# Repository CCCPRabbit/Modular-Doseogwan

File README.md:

# Modular Doseogwan

## Introduction

This project includes KiCad symbols, schematics, and program libraries.

## Contents

- KiCad Symbols
- Schematics
- Program Libraries

## License

This project is licensed under **CC-BY-NC-SA 4.0**.

- **BY** (Attribution): You must give appropriate credit to the original author.
- **NC** (NonCommercial): You may not use the material for commercial purposes.
- **SA** (ShareAlike): If you remix, transform, or build upon the material, you must distribute your contributions under the same license.

For more details, see the [Creative Commons license page](https://creativecommons.org/licenses/by-nc-sa/4.0/).

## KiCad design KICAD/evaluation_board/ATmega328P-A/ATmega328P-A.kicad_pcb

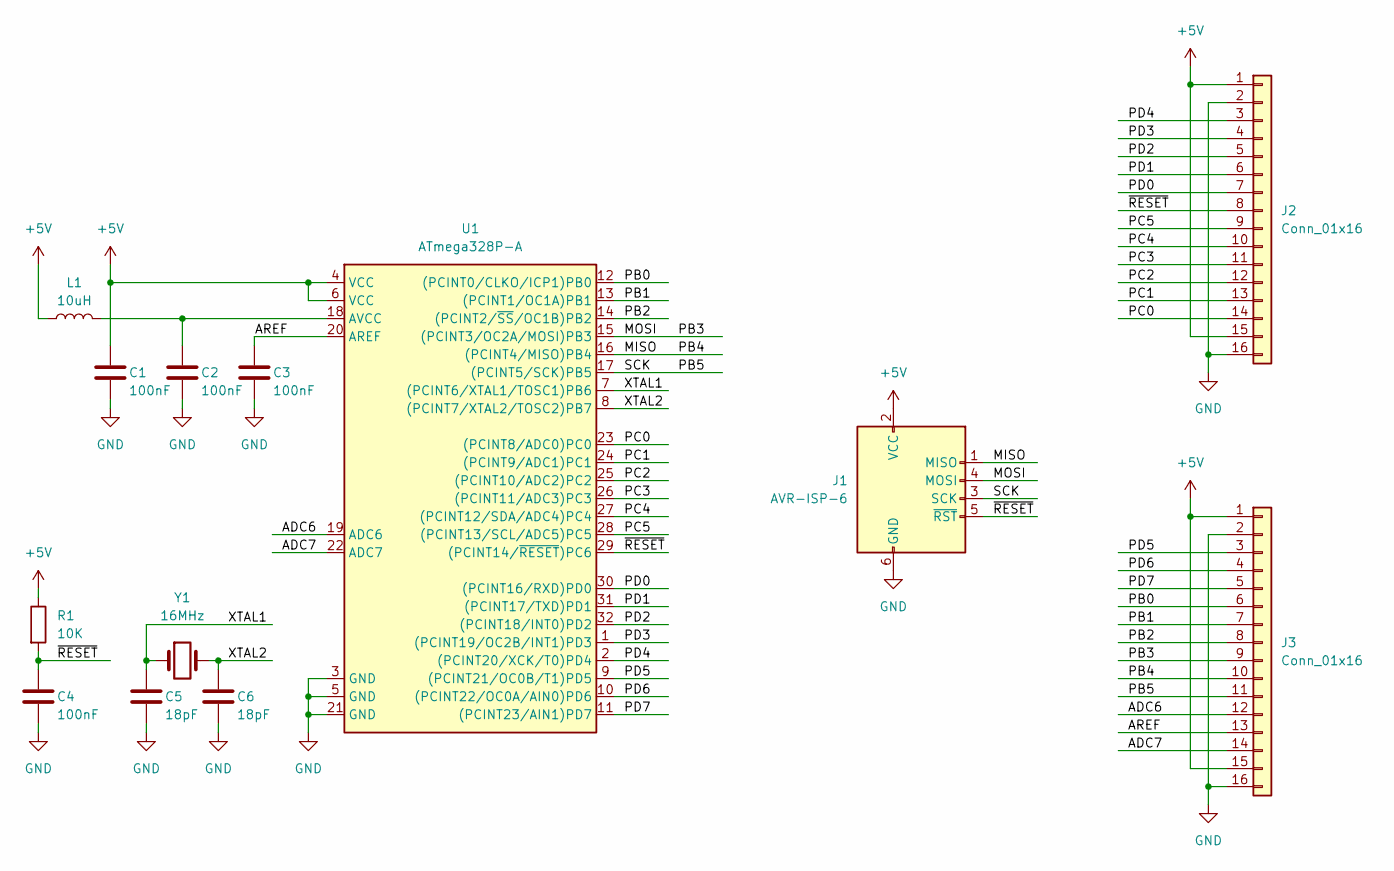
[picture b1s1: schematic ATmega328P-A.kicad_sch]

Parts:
C1, C2, C3, C4: 100nF; C_0603_1608Metric
C5, C6: 18pF; C_0603_1608Metric
J1: AVR-ISP-6; IDC-Header_2x03_P2.54mm_Vertical
J2, J3: Conn_01x16; PinHeader_1x16_P2.54mm_Vertical
L1: 10uH; L_0603_1608Metric
R1: 10K; R_0603_1608Metric
U1: ATmega328P-A; TQFP-32_7x7mm_P0.8mm
Y1: 16MHz; Crystal_SMD_HC49-SD

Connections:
+5V: C1.1, J1.2 (VCC), J2.1, J2.15, J3.1, J3.15, L1.1, R1.1, U1.4 (VCC), U1.6 (VCC)
/ADC6: J3.12, U1.19 (ADC6)
/ADC7: J3.14, U1.22 (ADC7)
/AREF: C3.1, J3.13, U1.20 (AREF)
/MISO: J1.1 (MISO), J3.10, U1.16 ((PCINT4/MISO)PB4)
/MOSI: J1.4 (MOSI), J3.9, U1.15 ((PCINT3/OC2A/MOSI)PB3)
/PB0: J3.6, U1.12 ((PCINT0/CLKO/ICP1)PB0)
/PB1: J3.7, U1.13 ((PCINT1/OC1A)PB1)
/PB2: J3.8, U1.14 ((PCINT2/~SS/OC1B)PB2)
/PB5: J1.3 (SCK), J3.11, U1.17 ((PCINT5/SCK)PB5)
/PC0: J2.14, U1.23 ((PCINT8/ADC0)PC0)
/PC1: J2.13, U1.24 ((PCINT9/ADC1)PC1)
/PC2: J2.12, U1.25 ((PCINT10/ADC2)PC2)
/PC3: J2.11, U1.26 ((PCINT11/ADC3)PC3)
/PC4: J2.10, U1.27 ((PCINT12/SDA/ADC4)PC4)
/PC5: J2.9, U1.28 ((PCINT13/SCL/ADC5)PC5)
/PD0: J2.7, U1.30 ((PCINT16/RXD)PD0)
/PD1: J2.6, U1.31 ((PCINT17/TXD)PD1)
/PD2: J2.5, U1.32 ((PCINT18/INT0)PD2)
/PD3: J2.4, U1.1 ((PCINT19/OC2B/INT1)PD3)
/PD4: J2.3, U1.2 ((PCINT20/XCK/T0)PD4)
/PD5: J3.3, U1.9 ((PCINT21/OC0B/T1)PD5)
/PD6: J3.4, U1.10 ((PCINT22/OC0A/AIN0)PD6)
/PD7: J3.5, U1.11 ((PCINT23/AIN1)PD7)
/XTAL1: C5.1, U1.7 ((PCINT6/XTAL1/TOSC1)PB6), Y1.1
/XTAL2: C6.1, U1.8 ((PCINT7/XTAL2/TOSC2)PB7), Y1.2
/~RESET: C4.1, J1.5 (~RST), J2.8, R1.2, U1.29 ((PCINT14/~RESET)PC6)
GND: C1.2, C2.2, C3.2, C4.2, C5.2, C6.2, J1.6 (GND), J2.2, J2.16, J3.2, J3.16, U1.3 (GND), U1.5 (GND), U1.21 (GND)
unnamed: C2.1, L1.2, U1.18 (AVCC)

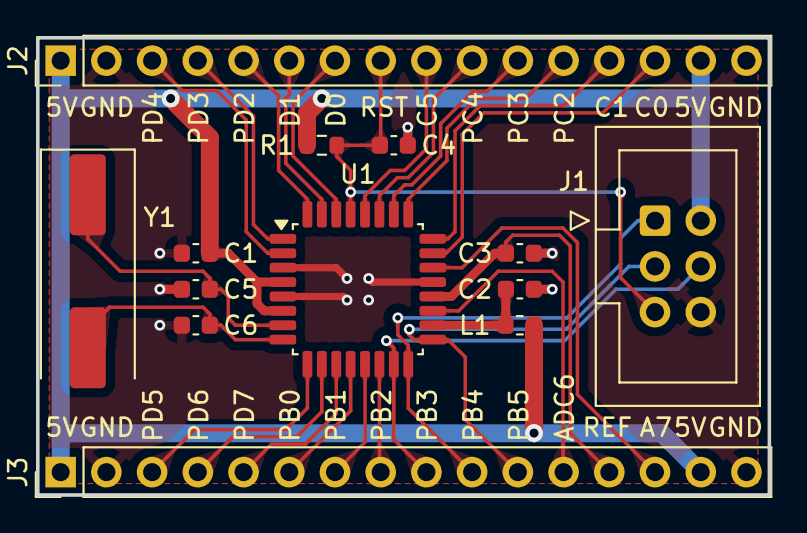
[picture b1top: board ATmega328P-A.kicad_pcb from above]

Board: 2 copper layers, 40.6 x 25.4 mm, 13 parts (0 on the bottom side), 29 nets.

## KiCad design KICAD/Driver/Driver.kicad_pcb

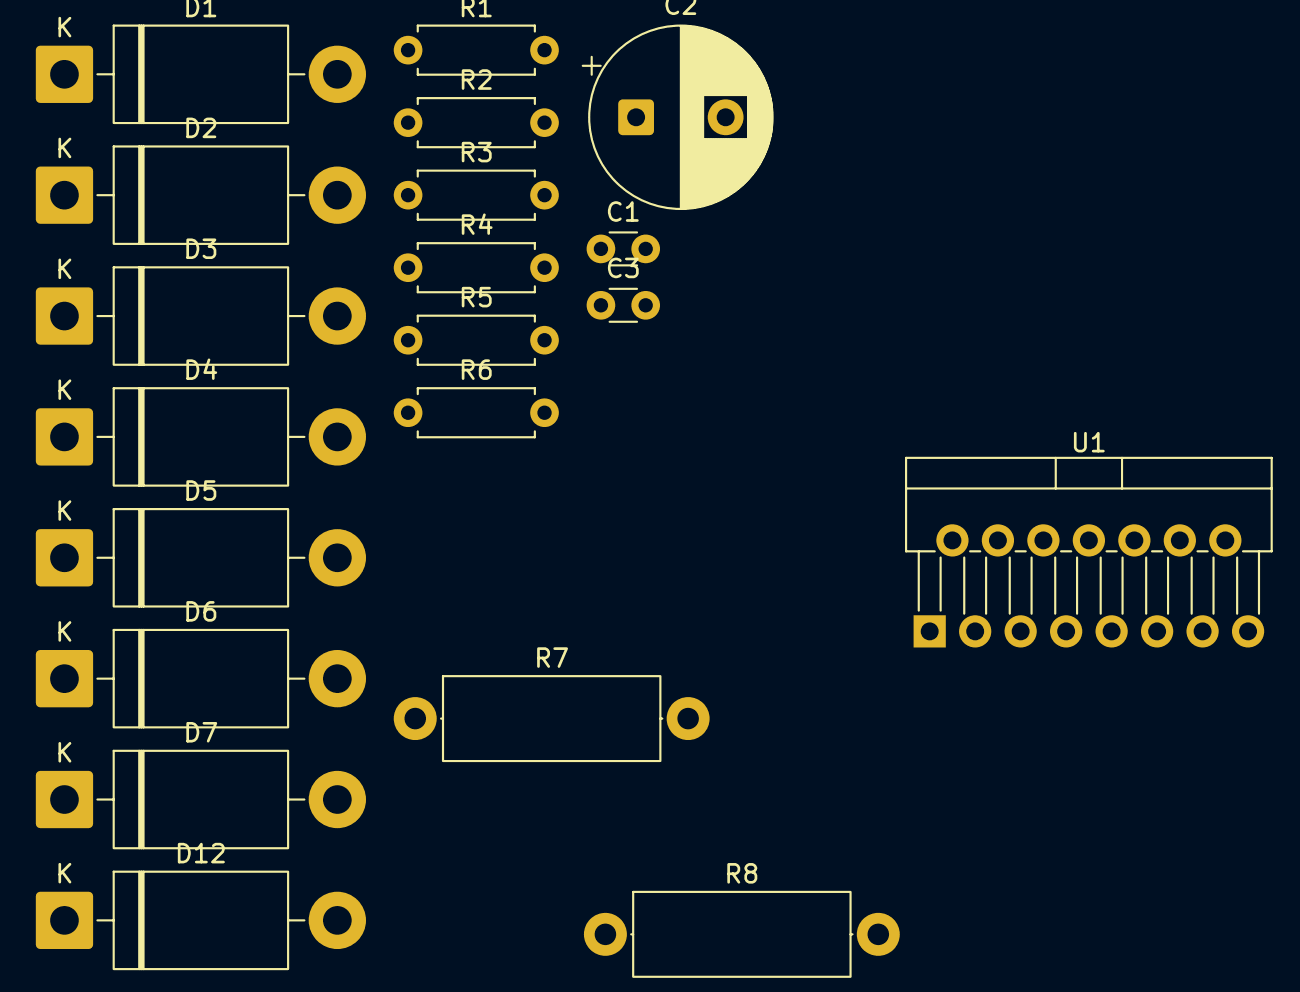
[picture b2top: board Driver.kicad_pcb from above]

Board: 2 copper layers, 20 parts (0 on the bottom side), 15 nets, no tracks yet.

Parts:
C1, C3: 100nF; C_Disc_D3.0mm_W1.6mm_P2.50mm
C2: 470uF/50V; CP_Radial_D10.0mm_P5.00mm
D1, D2, D3, D4, D5, D6, D7, D12: 1N5822; D_DO-201AD_P15.24mm_Horizontal
R1, R2, R3, R4, R5, R6: 100; R_Axial_DIN0207_L6.3mm_D2.5mm_P7.62mm_Horizontal
R7, R8: 0.25/1W; R_Axial_DIN0414_L11.9mm_D4.5mm_P15.24mm_Horizontal
U1: L298N; TO-220-15_P2.54x5.08mm_StaggerOdd_Lead4.58mm_Vertical

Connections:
+5V: C1.1, U1.9 (Vss)
+36V: C2.1, C3.1, D1.1 (K), D2.1 (K), D3.1 (K), D12.1 (K), U1.4 (Vs)
/L298/OUT1: D4.1 (K), D12.2 (A), U1.2 (OUT1)
/L298/OUT2: D1.2 (A), D5.1 (K), U1.3 (OUT2)
/L298/OUT3: D2.2 (A), D6.1 (K), U1.13 (OUT3)
/L298/OUT4: D3.2 (A), D7.1 (K), U1.14 (OUT4)
/L298/SENSE_A: R8.1, U1.1 (SENSE_A)
/L298/SENSE_B: R7.1, U1.15 (SENSE_B)
GND: C1.2, C2.2, C3.2, D4.2 (A), D5.2 (A), D6.2 (A), D7.2 (A), R7.2, R8.2, U1.8 (GND)
unnamed: R3.2, U1.6 (EnA)
unnamed: R6.2, U1.11 (EnB)
unnamed: R1.2, U1.5 (IN1)
unnamed: R2.2, U1.7 (IN2)
unnamed: R4.2, U1.10 (IN3)
unnamed: R5.2, U1.12 (IN4)

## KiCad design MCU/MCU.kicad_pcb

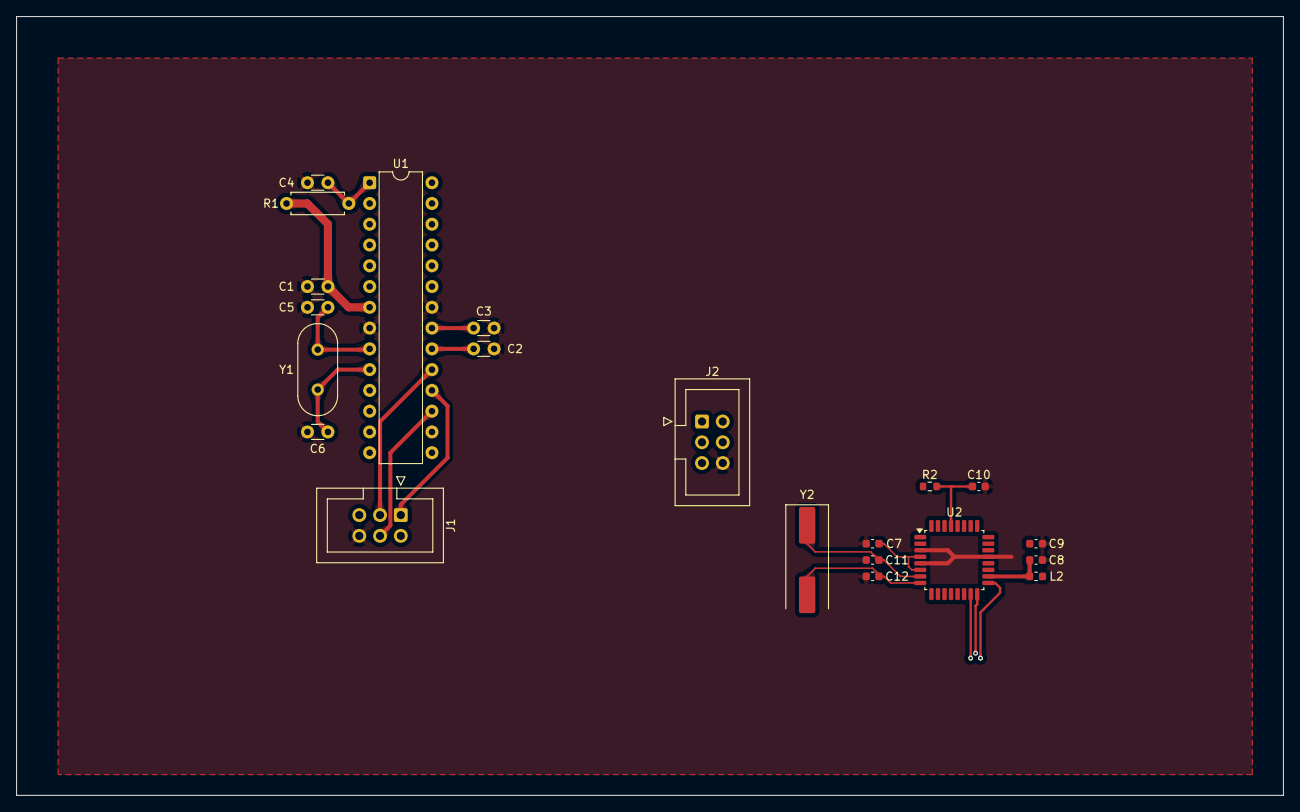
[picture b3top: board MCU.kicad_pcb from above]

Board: 2 copper layers, 154.9 x 95.2 mm, 21 parts (0 on the bottom side), 18 nets.

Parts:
C1, C2, C3, C4: 100nF; C_Disc_D3.0mm_W1.6mm_P2.50mm
C5, C6: 18pF; C_Disc_D3.0mm_W1.6mm_P2.50mm
C7, C8, C9, C10: 100nF; C_0603_1608Metric
C11, C12: 18pF; C_0603_1608Metric
J1, J2: AVR-ISP-6; IDC-Header_2x03_P2.54mm_Vertical
L2: 10uH; L_0603_1608Metric
R1: 10K; R_Axial_DIN0207_L6.3mm_D2.5mm_P7.62mm_Horizontal
R2: 10K; R_0603_1608Metric
U1: ATmega328P-P; DIP-28_W7.62mm
U2: ATmega328P-A; TQFP-32_7x7mm_P0.8mm
Y1: 16MHz/HC49-4H; Crystal_HC49-4H_Vertical
Y2: 16MHz/HC49-SD; Crystal_SMD_HC49-SD

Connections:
+5V: C1.1, C7.1, J1.2 (VCC), J2.2 (VCC), L2.1, R1.1, R2.1, U1.7 (VCC), U2.4 (VCC), U2.6 (VCC)
/ATmega328P-A/MISO: J2.1 (MISO), U2.16 ((PCINT4/MISO)PB4)
/ATmega328P-A/MOSI: J2.4 (MOSI), U2.15 ((PCINT3/OC2A/MOSI)PB3)
/ATmega328P-A/SCK: J2.3 (SCK), U2.17 ((PCINT5/SCK)PB5)
/ATmega328P-A/XTAL1: C11.1, U2.7 ((PCINT6/XTAL1/TOSC1)PB6), Y2.1
/ATmega328P-A/XTAL2: C12.1, U2.8 ((PCINT7/XTAL2/TOSC2)PB7), Y2.2
/ATmega328P-A/~RESET: C10.1, J2.5 (~RST), R2.2, U2.29 ((PCINT14/~RESET)PC6)
/ATmega328P-P/MISO: J1.1 (MISO), U1.18 ((PCINT4/MISO)PB4)
/ATmega328P-P/MOSI: J1.4 (MOSI), U1.17 ((PCINT3/OC2A/MOSI)PB3)
/ATmega328P-P/SCK: J1.3 (SCK), U1.19 ((PCINT5/SCK)PB5)
/ATmega328P-P/XTAL1: C5.1, U1.9 ((PCINT6/XTAL1/TOSC1)PB6), Y1.1
/ATmega328P-P/XTAL2: C6.1, U1.10 ((PCINT7/XTAL2/TOSC2)PB7), Y1.2
/ATmega328P-P/~RESET: C4.1, J1.5 (~RST), R1.2, U1.1 ((PCINT14/~RESET)PC6)
GND: C1.2, C2.2, C3.2, C4.2, C5.2, C6.2, C7.2, C8.2, C9.2, C10.2, C11.2, C12.2, J1.6 (GND), J2.6 (GND), U1.8 (GND), U1.22 (GND), U2.3 (GND), U2.5 (GND), U2.21 (GND)
unnamed: C3.1, U1.21 (AREF)
unnamed: C2.1, U1.20 (AVCC)
unnamed: C9.1, U2.20 (AREF)
unnamed: C8.1, L2.2, U2.18 (AVCC)

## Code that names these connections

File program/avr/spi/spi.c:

#include <avr/io.h>

#define SCK_DDR     DDRB
#define SCK_PIN     PB5
#define MOSI_DDR    DDRB
#define MOSI_PIN    PB3
#define MISO_DDR    DDRB
#define MISO_PIN    PB4
#define CS_DDR      DDRB
#define CS_PORT     PORTB
#define CS_PIN      PB2

void SPIInit(void)
{
    CS_PORT |= (1 << CS_PIN);
    SCK_DDR |= (1 << SCK_PIN);
    MOSI_DDR |= (1 << MOSI_PIN);
    CS_DDR |= (1 << CS_PIN);
    MISO_DDR &= ~(1 << MISO_PIN);
    
    // SPI 설정: Master, MSB first, Mode 0, F_CPU/16
    SPCR = (1 << SPE) | (1 << MSTR) | (1 << SPR0);
    SPSR = 0;
}

uint8_t SPITransmitByte(uint8_t data)
{
    SPDR=data;
    while (!(SPSR & (1 << SPIF)));
    return SPDR;
}

void SPITransmitMultiByte(uint8_t *tx_data,uint8_t *rx_data,uint8_t length)
{
    for(uint8_t i=0;i<length;i++)
    {
        SPDR=tx_data[i];
        while (!(SPSR & (1 << SPIF)));
        rx_data[i]=SPDR;
    }
}

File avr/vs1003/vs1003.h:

#ifndef _VS1003_H
#define _VS1003_H

#include <avr/io.h>
#include <util/delay.h>
#include "spi.h"

// 핀 정의
#define VS_DREQ_PORT    PORTD
#define VS_DREQ_PIN_REG PIND
#define VS_DREQ_PIN     PD2
#define VS_XDCS_DDR     DDRB
#define VS_XDCS_PORT    PORTB
#define VS_XDCS_PIN     PB1
#define VS_XCS_DDR      DDRB
#define VS_XCS_PORT     PORTB
#define VS_XCS_PIN      PB2
#define VS_RESET_DDR    DDRB
#define VS_RESET_PORT   PORTB
#define VS_RESET_PIN    PB0

// VS1003 명령어
#define VS_WRITE_CMD 0x02
#define VS_READ_CMD  0x03

// VS1003 레지스터 주소
#define SCI_MODE        0x00
#define SCI_STATUS      0x01
#define SCI_BASS        0x02
#define SCI_CLOCKF      0x03
#define SCI_DECODE_TIME 0x04
#define SCI_AUDATA      0x05
#define SCI_WRAM        0x06
#define SCI_WRAMADDR    0x07
#define SCI_HDAT0       0x08
#define SCI_HDAT1       0x09
#define SCI_AIADDR      0x0A
#define SCI_VOL         0x0B

//SCI_MODE_BIT
#define SM_OUTOFWAV 0x0008

// 함수 원형
void VS1003_Init(void);
void VS1003_WriteRegister(uint8_t address, uint16_t value);
uint16_t VS1003_ReadRegister(uint8_t address);
void VS1003_SendMusicData(uint8_t *data, uint8_t length);
void VS1003_SetVolume(uint8_t left, uint8_t right);

#endif // _VS1003_H

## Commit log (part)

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2026-03-15 add source code
